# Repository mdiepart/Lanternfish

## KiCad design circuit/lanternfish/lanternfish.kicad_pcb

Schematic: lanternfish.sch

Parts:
BT1: CR2032; Renata_cr2032_CMS
C1, C2, C15: 10nF; C_1206_3216Metric_Pad1.42x1.75mm_HandSolder
C3, C6, C14: 10uF; C_1206_3216Metric_Pad1.42x1.75mm_HandSolder
C4, C9, C12, C13: 0.1uF; C_1206_3216Metric_Pad1.42x1.75mm_HandSolder
C5: 0.33uF; C_1206_3216Metric_Pad1.42x1.75mm_HandSolder
C7, C8: 6pF; C_1206_3216Metric_Pad1.42x1.75mm_HandSolder
D1: BZX84W-B13X; SOT-323_SC-70_Handsoldering
DS1: LCM1602; lcm1602
H1, H2, H3, H4: MountingHole; MountingHole_2.2mm_M2_Pad_Via
J1: Input; MC000048
J2: Prog; PinHeader_2x03_P2.54mm_Vertical
J3: Output; MC000048
Q1: FQD17P06TM; TO-252-3_TabPin2
Q2: PSMN5R6-60YLX; LFPAK56
Q3: SI2302DDS-T1-GE3; SOT-23_Handsoldering
R1, R2, R3, R4, R6, R7, R8, R9, R10, R11, R15, R16, R17, R18, R19, R20, R21, R25: 10kR; R_0805_2012Metric_Pad1.15x1.40mm_HandSolder
R5: 100kR; R_1206_3216Metric_Pad1.42x1.75mm_HandSolder
R12, R22, R23, R24: 220R; R_1206_3216Metric_Pad1.42x1.75mm_HandSolder
RV1: 10kR; RC33X-2
SW1, SW2: SW_Push; PinHeader_1x02_P2.54mm_Vertical
SW3: PEC11R-4215F-S0024
SW6: SW_SPST; PinHeader_1x02_P2.54mm_Vertical
U1: MCP7940N-xMS; SOIC-8_3.9x4.9mm_P1.27mm
U2: L7805; TO-252-3_TabPin2
U3: ATmega328PB-AU; TQFP-32_7x7mm_P0.8mm
Y1: ABS25-32.768KHZ-6-1-T; Abracon_ABS25_4Pin_8mm_3.8mm

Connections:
+5V: C4.1, C9.2, C12.1, C13.2, DS1.2 (VDD), J2.6, R1.1, R6.1, R7.1, R8.1, R10.1, R11.1, R15.2, R17.1, R18.1, R19.1, R20.1, R21.1, R24.1, RV1.3, U1.8 (VCC), U2.3 (OUT), U3.4 (VCC), U3.18 (AVCC)
+BATT: BT1.1 (+), U1.3 (VBAT)
/Gate: R22.2, R23.2, U3.9 (PD5)
/LCD_BL: R12.1, U3.10 (PD6)
/LCD_D0: DS1.7 (D0), U3.23 (PC0)
/LCD_D1: DS1.8 (D1), U3.11 (PD7)
/LCD_D2: DS1.9 (D2), U3.30 (PD0)
/LCD_D3: DS1.10 (D3), U3.24 (PC1)
/LCD_D4: DS1.11 (D4), U3.2 (PD4)
/LCD_D5: DS1.12 (D5), U3.31 (PD1)
/LCD_D6: DS1.13 (D6), U3.25 (PC2)
/LCD_D7: DS1.14 (D7), U3.26 (PC3)
/LCD_E: DS1.6 (E), U3.12 (PB0)
/LCD_RS: DS1.4 (RS), U3.14 (PB2)
/LCD_RW: DS1.5 (R/W), U3.13 (PB1)
/MISO: J2.1, U3.16 (PB4)
/MOSI: J2.5, U3.15 (PB3)
/ROT_SW_A: C1.1, R3.2, U3.32 (PD2)
/ROT_SW_B: C2.1, R4.1, U3.1 (PD3)
/RST: J2.3, R17.2, U3.29 (~RESET~/PC6)
/RTC_MSP: R11.2, U1.7 (MFP), U3.19 (PE2)
/SCK: J2.2, U3.17 (PB5)
/SCL: R18.2, R19.2, U1.6 (SCL), U3.28 (PC5)
/SDA: R20.2, R21.2, U1.5 (SDA), U3.27 (PC4)
/SW1: C3.1, R2.2, U3.3 (PE0)
/SW2: C6.1, R9.2, U3.6 (PE1)
/SW_MAN: C14.1, R16.1, U3.8 (XTAL2/PB7)
/SW_SEL: C15.1, R25.1, U3.7 (XTAL1/PB6)
GND: BT1.2 (-), C1.2, C2.2, C3.2, C4.2, C5.1, C6.2, C7.2, C8.2, C9.1, C12.2, C13.1, C14.2, C15.2, DS1.1 (VSS), J1.2, J2.4, Q2.1, Q2.2, Q2.3, Q3.2 (S), R5.2, RV1.1, SW1.1, SW2.1, SW3.C, SW3.S2, SW6.1 (A), U1.4 (VSS), U2.2 (GND), U3.5 (GND), U3.21 (GND)
unnamed: C7.1, U1.1 (X1), Y1.1
unnamed: C8.1, U1.2 (X2), Y1.4 (2)
unnamed: D1.1 (A), Q1.1 (G), R5.1
unnamed: DS1.3 (VO), RV1.2
unnamed: DS1.15 (LED(+)), R24.2
unnamed: DS1.16 (LED(-)), Q3.3 (D)
unnamed: J1.1, Q1.2 (D)
unnamed: J3.2, Q2.5
unnamed: Q2.4, R22.1, R23.1
unnamed: Q3.1 (G), R12.2
unnamed: R1.2, R2.1, SW1.2
unnamed: R3.1, R7.2, SW3.A
unnamed: R4.2, R6.2, SW3.B
unnamed: R8.2, R9.1, SW2.2
unnamed: R10.2, R25.2, SW3.S1
unnamed: R15.1, R16.2, SW6.2 (B)
VDD: C5.2, D1.3 (K), J3.1, Q1.3 (S), U2.1 (IN)

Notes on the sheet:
Auto/Man
Rotary switch
Polarity protection
5V regulator
Power supply
Switches
Real Time Clock
Output switching
Programming interface
LCD Module
PCINT27
PCINT26
PCINT25
PCINT24
D10
D11
D12
D13
PCINT6
PCINT7

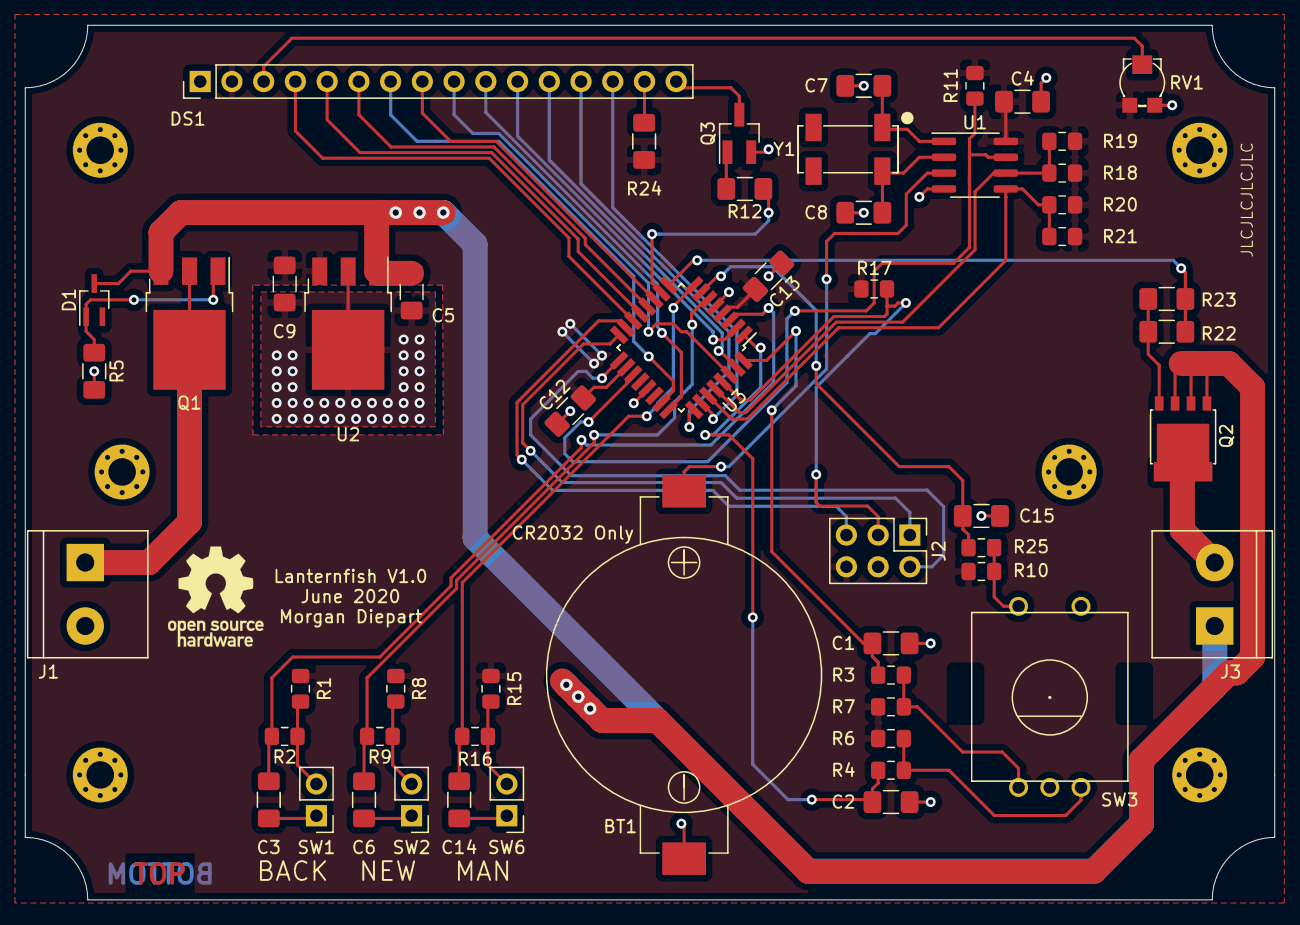
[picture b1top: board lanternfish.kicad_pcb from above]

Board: 2 copper layers, 100.0 x 70.0 mm, 58 parts (0 on the bottom side), 46 nets.

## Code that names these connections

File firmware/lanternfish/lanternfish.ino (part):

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
typedef unsigned short int bcd;

LiquidCrystal lcd(PIN_PB2, PIN_PB1, PIN_PB0, PIN_PC0, PIN_PD7, PIN_PD0, PIN_PC1,
                  PIN_PD4, PIN_PD1, PIN_PC2, PIN_PC3);
Encoder knob(PIN_PD3, PIN_PD2);

DaySchedule schedule(0);

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
void setup() {
  /* Rot switch :
   *  A = D2 (PD2)
   *  B = D3 (PD3)
   *  PB = / (PCINT6) (PCIE0)
   *  
   *  LCD :
   *  RS = D10 = PB2
   *  RW = D9 = PB1
   *  enable = D8 = PB0
   *  LCD_D0 = A0 = PC0
   *  LCD_D1 = D7 = PD7
   *  LCD_D2 = D0 = PD0
   *  LCD_D3 = A1 = PC1
   *  LCD_D4 = D4 = PD4
   *  LCD_D5 = D1 = PD1
   *  LCD_D6 = A2 = PC2
   *  LCD_D7 = A3 = PC3
   *  Backlight = D6 = PD6
   *  
   *  Switches :
   *  BACK (1) = / (PCINT24) (PCIE3)
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   *  MAN     = / (PCINT7) (PCIE0)
   *  
   *  Output :
   *  Gate = D5
   *  
   *  RTC : 1101111+(R/~W)
   *  I2C
   *  MSP = PE2 (PCINT26)
   */

  /*Configures LCD*/
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  lcd.noCursor();
  delay(1000);
  /* Configures pins */
  pinMode(PIN_PD5, OUTPUT); // Gate
  pinMode(PIN_PD6, OUTPUT); // LCD Backlight
  pinMode(PIN_PB6, INPUT);
  pinMode(PIN_PB7, INPUT);
  pinMode(PIN_PE0, INPUT);
  pinMode(PIN_PE1, INPUT);  

  /* Configures I2C */
  Wire.begin();
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
  // Load data points for today
  schedule.changeDay(_dow);
  digitalWrite(PIN_PD6, HIGH);

  /*  
   *   Init man mode
   */

   swManStat = (PINB & (1 << PB7)) != 0;
  /*
   * Enabling PinChangeInterrupt
   */
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}

ISR(PCINT0_vect){
  bool swMan = (PINB & (1 << PB7)) != 0;
  bool swSel = (PINB & (1 << PB6)) != 0;
  
  lastActivity = millis();

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}

ISR(PCINT3_vect){
  bool swBack = (PINE & (1 << PE0)) != 0;
  bool swNew = (PINE & (1 << PE1)) != 0;
  lastActivity = millis();

  /*
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
  /* checks if we have to shutdown LCD */
  if (millis() - lastActivity >= LCD_TIMEOUT) {
    digitalWrite(PIN_PD6, LOW);
  } else {
    digitalWrite(PIN_PD6, HIGH);
  }

  if (swManStat == true) { // Manual mode
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    swSelStat = 0;
    swBackStat = false;
    swNewStat = false;
    analogWrite(PIN_PD5, manPower*2.55);
  } else { //Schedule mode
    //Check if we have to fetch time from RTC
    if (millis() - lastRTCRead > RTC_UPDATE_INTERVAL) {
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
      // Updates power
      unsigned char power = schedule.getPower(_timeH, _timeM, _timeS);
      analogWrite(PIN_PD5, power);
    }
    //Updates the menu state (and LCD content)
    updateMenu(knobVal, swSelStat, swBackStat, swNewStat);
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
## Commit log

2020-06-22 Designed hardware circuit
2020-06-23 Updated PCB
    Added mounting hole + rounded corners
2020-06-23 Creating box [WIP]
2020-06-24 Updated circuit [wip]
    Removed 2 switches, connected MFP from RTC to MCU
    Updated 25V netclass
2020-06-24 Continued enclosure design [WIP]
2020-06-25 Deleted backup file
2020-06-25 Updated enclosure [wip]
2020-06-25 updated enclosure
2020-06-25 Updated circuit
2020-06-27 Updated LCD Fixations
2020-06-27 Updated box
    Raised walls, moved LCD window
2020-06-28 Added interactive HTML BOM
2020-06-28 Writing firmware [WIP]
2020-08-31 Updated variable names and comments
2020-08-31 Added strings
2020-09-19 fixed EEPROM addresses in schedule
2020-09-19 Removed useless save() while adding points to schedule in main file
2020-09-19 Load previous day last and next day first values in schedule
2020-09-20 adding seconds to time readings from rtc
2020-09-20 Adding power computation function
2020-09-20 Main file updates power
2020-09-20 various fixes
2020-09-21 Fixed various bugs in daySchedule
2020-09-21 Added STR_MAN string
2020-09-21 Updated main loop
2020-09-28 Debug [WIP]
2020-09-28 Added padding to lcd strings
